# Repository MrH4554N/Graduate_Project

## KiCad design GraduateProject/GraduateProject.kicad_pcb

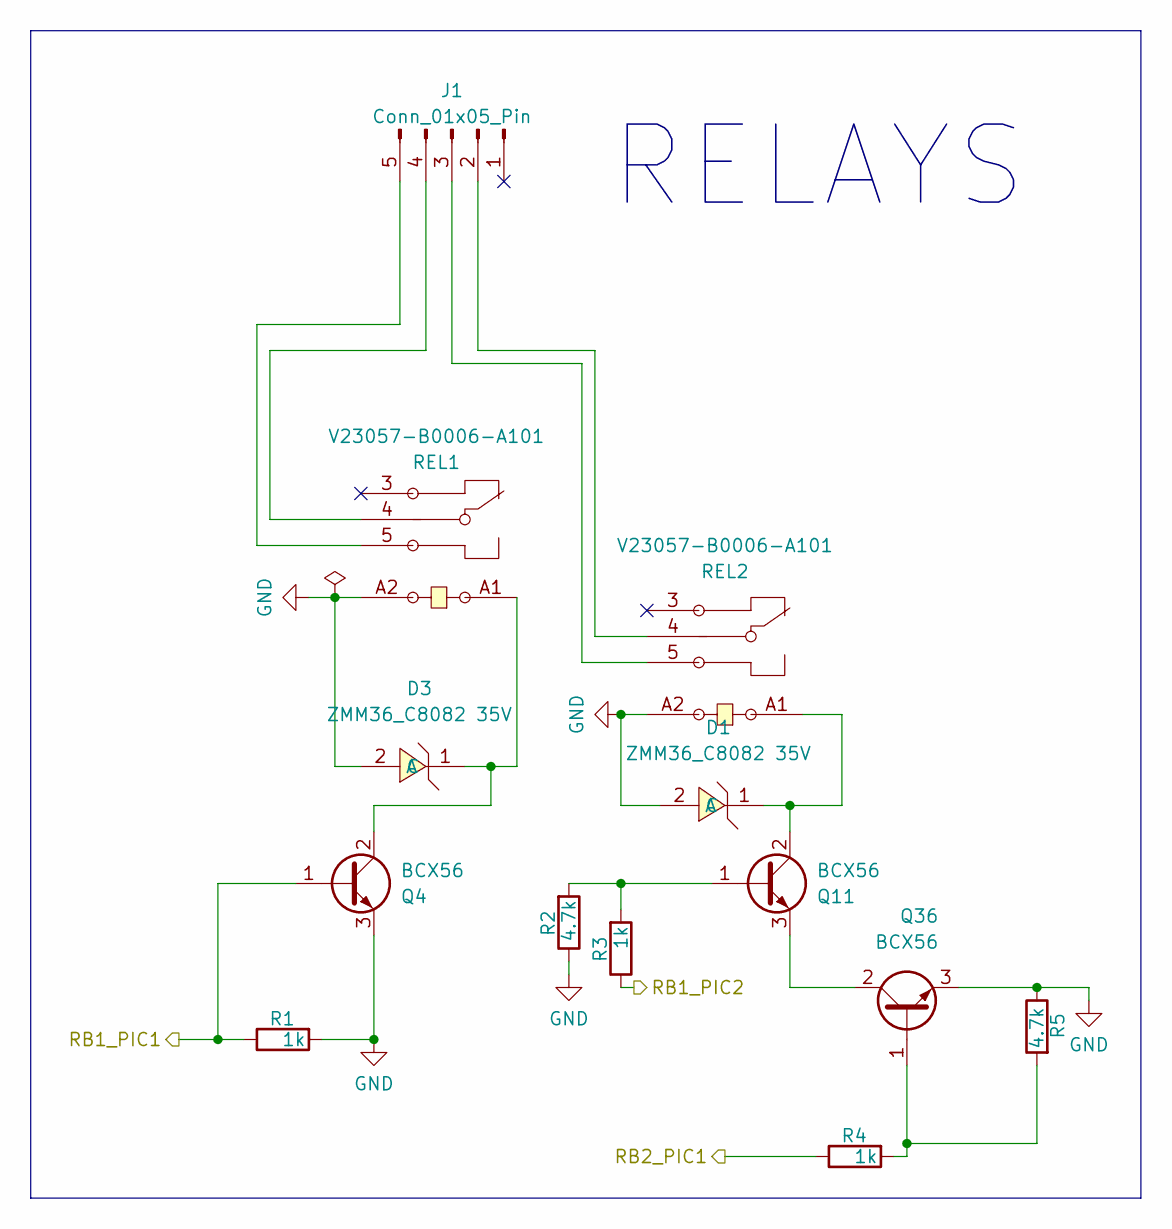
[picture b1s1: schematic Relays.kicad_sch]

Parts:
D1, D3: ZMM36_C8082 35V; LL-34_L3.5-W1.5-RD; LCSC Part C8082
J1: Conn_01x05_Pin; PinHeader_1x05_P2.54mm_Vertical
Q4, Q11, Q36: BCX56; SOT-89-3
R1, R3, R4: 1k; R_0805_2012Metric
R2, R5: 4.7k; R_0805_2012Metric
REL1, REL2: V23057-B0006-A101; RELAY-TH_TE_V23057BXXX; LCSC Part C1564084

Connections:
/PICs/RB1_PIC1: Q4.1 (B), R1.1; also elsewhere on the board
/PICs/RB1_PIC2: R3.1; also elsewhere on the board
/PICs/RB2_PIC1: R4.1; also elsewhere on the board
GND: D1.2 (A), D3.2 (A), Q4.3 (E), Q36.3 (E), R1.2, R2.1, R5.1, REL1.A2, REL2.A2; also elsewhere on the board
unnamed: D1.1 (C), Q11.2 (C), REL2.A1
unnamed: D3.1 (C), Q4.2 (C), REL1.A1
unnamed: J1.2, REL2.4
unnamed: J1.3, REL2.5
unnamed: J1.4, REL1.4
unnamed: J1.5, REL1.5
unnamed: Q11.1 (B), R2.2, R3.2
unnamed: Q11.3 (E), Q36.2 (C)
unnamed: Q36.1 (B), R4.2, R5.2

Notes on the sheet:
RELAYS

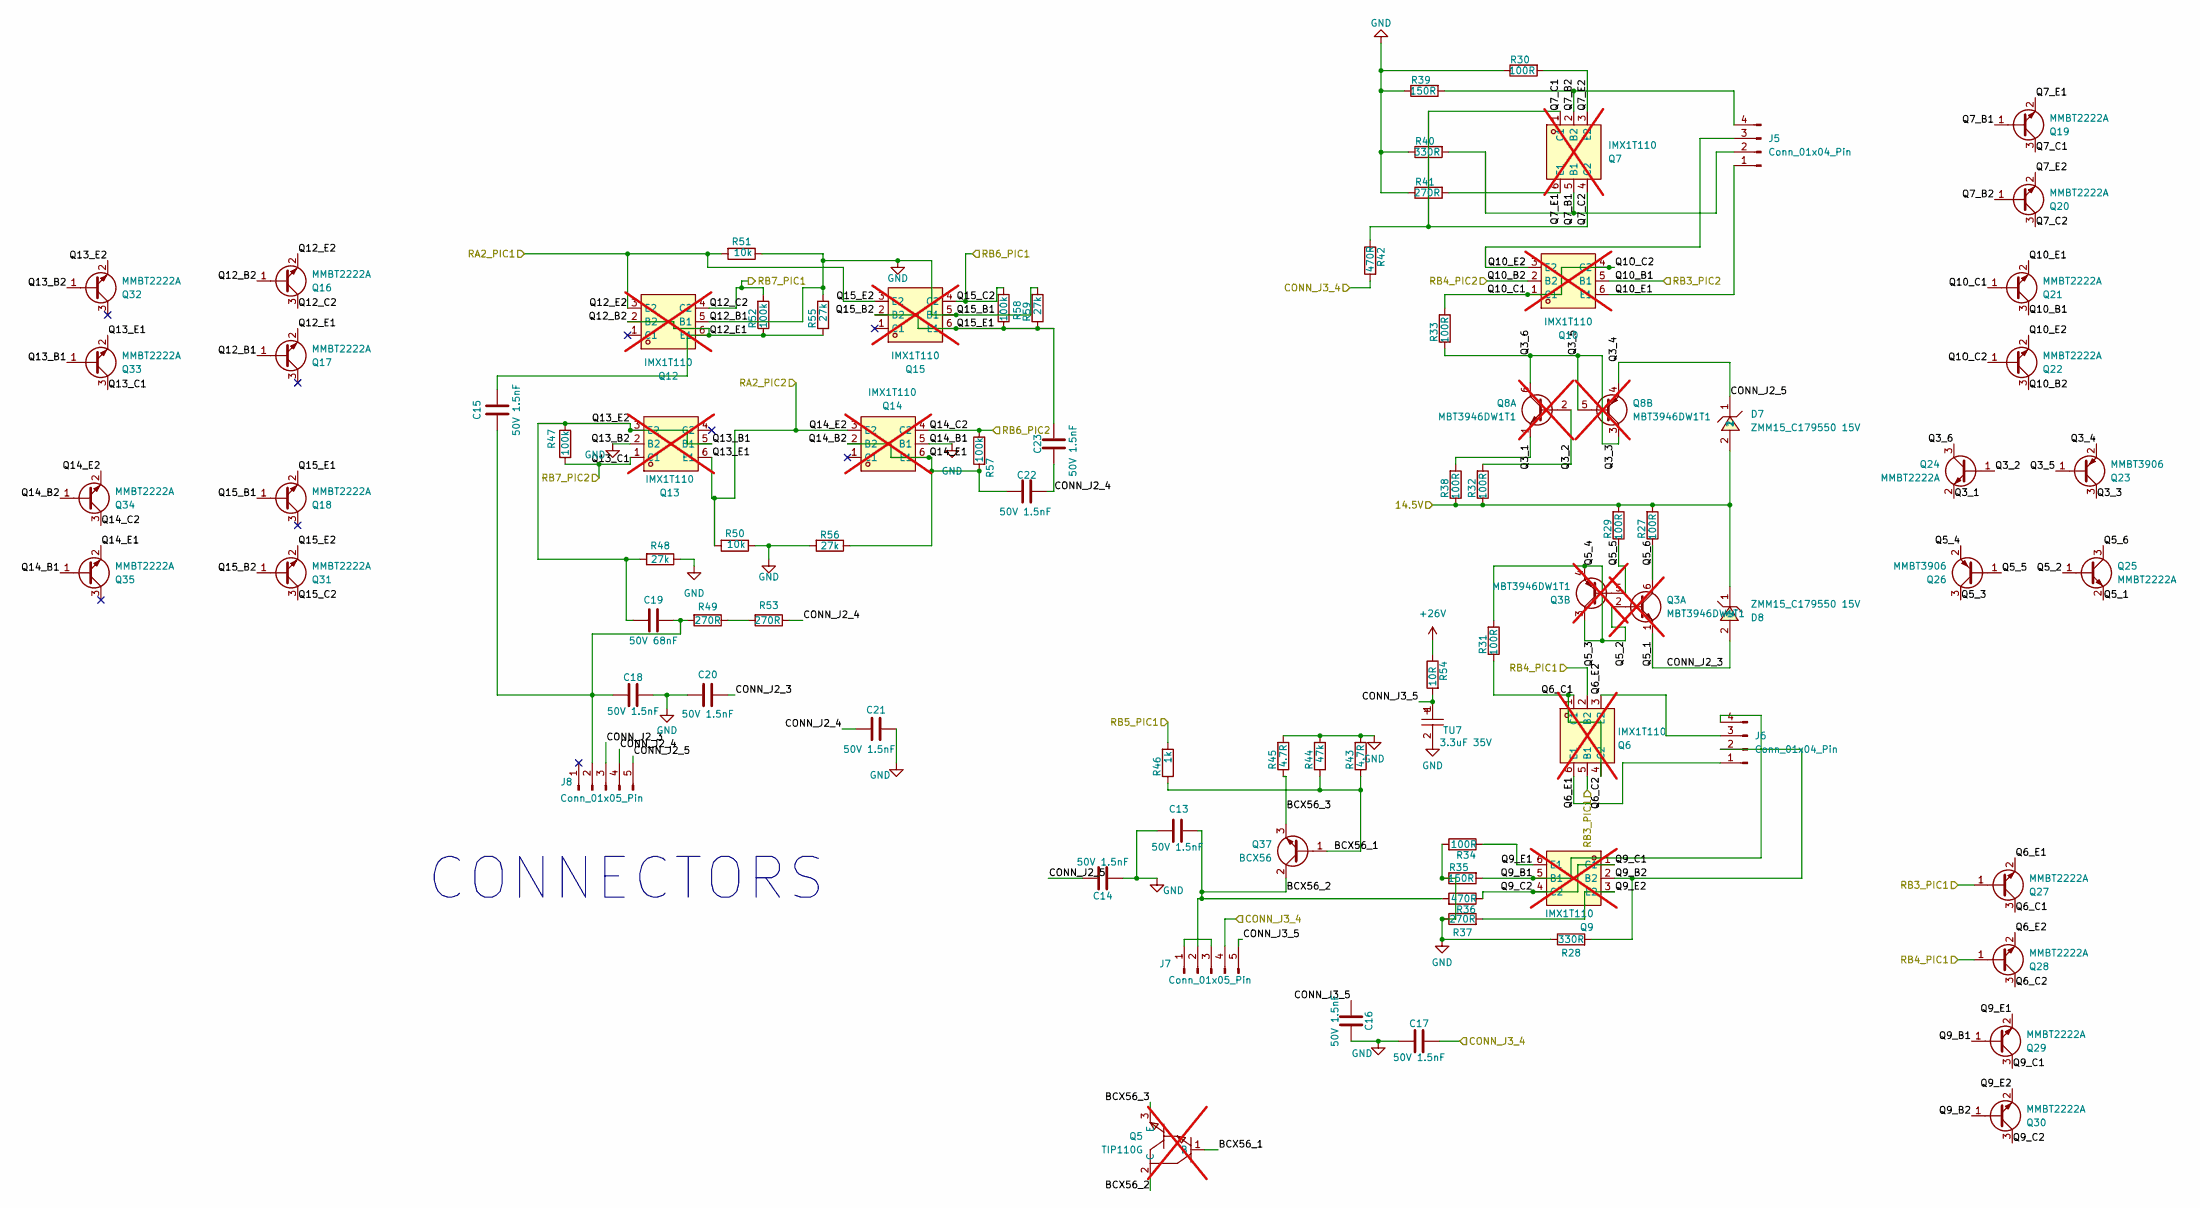
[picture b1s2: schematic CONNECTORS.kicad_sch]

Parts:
C13, C14, C15, C16, C17, C18, C20, C21, C22, C23: 50V 1.5nF; C_0805_2012Metric
C19: 50V 68nF; C_0805_2012Metric
D7, D8: ZMM15_C179550 15V; SOD-80_L3.5-W1.5-RD; LCSC Part C179550
J5, J6: Conn_01x04_Pin; PinHeader_1x04_P2.54mm_Vertical
J7, J8: Conn_01x05_Pin; PinHeader_1x05_P2.54mm_Vertical
Q3, Q8: MBT3946DW1T1; SOT-363_SC-70-6; not fitted
Q5: TIP110G; TO-220-3_L10.0-W4.5-P2.54-L; LCSC Part C233760; not fitted
Q6, Q7, Q9, Q10, Q12, Q13, Q14, Q15: IMX1T110; SOT-457_L2.9-W1.6-P0.95-LS2.80-BR; LCSC Part C509893; not fitted
Q16, Q17, Q18, Q19, Q20, Q21, Q22, Q24, Q25, Q27, Q28, Q29, Q30, Q31, Q32, Q33, Q34, Q35: MMBT2222A; SOT-23
Q23, Q26: MMBT3906; SOT-23
Q37: BCX56; SOT-89-3
R27, R29, R30, R31, R32, R33, R34, R38: 100R; R_0805_2012Metric
R28, R40: 330R; R_0805_2012Metric
R35, R39: 150R; R_0805_2012Metric
R36, R42: 470R; R_0805_2012Metric
R37, R41, R49, R53: 270R; R_0805_2012Metric
R43, R45: 4.7R; R_0805_2012Metric
R44: 47k; R_0805_2012Metric
R46: 1k; R_0805_2012Metric
R47, R52, R57, R58: 100k; R_0805_2012Metric
R48, R55, R56, R59: 27k; R_0805_2012Metric
R50, R51: 10k; R_0805_2012Metric
R54: 10R; R_0805_2012Metric
TU7: 3.3uF 35V; CAP-SMD_L3.5-W2.8-R-RD; LCSC Part C7201

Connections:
+26V: R54.1; also elsewhere on the board
/CONNECTORS/14.5V: D7.2, D8.1, R27.2, R29.2, R32.1, R38.1; also elsewhere on the board
/CONNECTORS/BCX56_1: Q5.1 (B), Q37.1 (B), R43.1, R44.1, R46.1
/CONNECTORS/BCX56_2: C13.1, J7.2, Q5.2 (C), Q37.2 (C), R36.2
/CONNECTORS/BCX56_3: Q5.3 (E), Q37.3 (E), R45.1
/CONNECTORS/CONN_J2_3: C20.1, D8.2, J8.3, Q3.1 (E1), Q25.2 (E)
/CONNECTORS/CONN_J2_4: C21.1, C22.1, C23.2, J8.4, R53.1
/CONNECTORS/CONN_J2_5: C14.1, D7.1, J8.5, Q8.4 (E2), Q23.2 (E)
/CONNECTORS/CONN_J3_4: C17.2, J7.4, R42.2; also elsewhere on the board
/CONNECTORS/CONN_J3_5: C16.1, J7.5, R54.2, TU7.1
/CONNECTORS/Q3_1: Q8.1 (E1), Q24.2 (E), R38.2
/CONNECTORS/Q3_2: Q8.2 (B1), Q24.1 (B), R32.2
/CONNECTORS/Q3_3: Q8.3 (C2), Q8.5 (B2), Q8.6 (C1), Q23.1 (B), Q23.3 (C), Q24.3 (C), R33.1
/CONNECTORS/Q5_2: Q3.2 (B1), Q3.3 (C2), Q3.4 (E2), Q25.1 (B), Q26.2 (E), Q26.3 (C), R31.2
/CONNECTORS/Q5_5: Q3.5 (B2), Q26.1 (B), R29.1
/CONNECTORS/Q5_6: Q3.6 (C1), Q25.3 (C), R27.1
/CONNECTORS/Q6_C1: Q6.1 (C1), Q6.4 (C2), Q27.3 (C), Q28.3 (C), R31.1
/CONNECTORS/Q6_E1: J6.1, Q6.6 (E1), Q27.2 (E)
/CONNECTORS/Q6_E2: J6.3, Q6.3 (E2), Q28.2 (E)
/CONNECTORS/Q7_B1: J5.2, Q7.5 (B1), Q19.1 (B), R40.2
/CONNECTORS/Q7_B2: J5.4, Q7.2 (B2), Q20.1 (B), R39.2
/CONNECTORS/Q7_C1: Q7.1 (C1), Q7.4 (C2), Q19.3 (C), Q20.3 (C), R42.1
/CONNECTORS/Q7_E1: Q7.6 (E1), Q19.2 (E), R41.2
/CONNECTORS/Q7_E2: Q7.3 (E2), Q20.2 (E), R30.2
/CONNECTORS/Q9_B1: J6.4, Q9.5 (B1), Q29.1 (B), R35.2
/CONNECTORS/Q9_B2: J6.2, Q9.2 (B2), Q30.1 (B), R28.2
/CONNECTORS/Q9_C1: Q9.1 (C1), Q9.4 (C2), Q29.3 (C), Q30.3 (C), R36.1
/CONNECTORS/Q9_E1: Q9.6 (E1), Q29.2 (E), R34.1
/CONNECTORS/Q9_E2: Q9.3 (E2), Q30.2 (E), R37.2
/CONNECTORS/Q10_B1: Q10.5 (B1), Q21.3 (C); also elsewhere on the board
/CONNECTORS/Q10_B2: Q10.2 (B2), Q22.3 (C); also elsewhere on the board
/CONNECTORS/Q10_C1: Q10.1 (C1), Q10.4 (C2), Q21.1 (B), Q22.1 (B), R33.2
/CONNECTORS/Q10_E1: J5.1, Q10.6 (E1), Q21.2 (E)
/CONNECTORS/Q10_E2: J5.3, Q10.3 (E2), Q22.2 (E)
/CONNECTORS/Q12_B2: C15.2, Q12.2 (B2), Q12.6 (E1), Q16.1 (B), Q17.2 (E), R52.1, R55.1
/CONNECTORS/Q12_C2: Q12.4 (C2), Q16.3 (C), R52.2; also elsewhere on the board
/CONNECTORS/Q12_E2: Q12.3 (E2), Q15.3 (E2), Q16.2 (E), Q31.2 (E), R51.2; also elsewhere on the board
/CONNECTORS/Q13_B1: C19.2, Q13.3 (E2), Q13.5 (B1), Q32.2 (E), Q33.1 (B), R47.1, R48.2
/CONNECTORS/Q13_C1: Q13.1 (C1), Q33.3 (C), R47.2; also elsewhere on the board
/CONNECTORS/Q13_E1: Q13.6 (E1), Q14.3 (E2), Q33.2 (E), Q34.2 (E), R50.2; also elsewhere on the board
/CONNECTORS/Q14_B2: C22.2, Q14.2 (B2), Q14.6 (E1), Q34.1 (B), Q35.2 (E), R56.1, R57.2
/CONNECTORS/Q14_C2: Q14.4 (C2), Q34.3 (C), R57.1; also elsewhere on the board
/CONNECTORS/Q15_B2: C23.1, Q15.2 (B2), Q15.6 (E1), Q18.2 (E), Q31.1 (B), R58.1, R59.1
/CONNECTORS/Q15_C2: Q15.4 (C2), Q31.3 (C), R58.2; also elsewhere on the board
/CONNECTORS/RB3_PIC1: Q6.5 (B1), Q27.1 (B); also elsewhere on the board
/CONNECTORS/RB4_PIC1: Q6.2 (B2), Q28.1 (B); also elsewhere on the board
/CONNECTORS/RB5_PIC1: R46.2; also elsewhere on the board
GND: C13.2, C14.2, C16.2, C17.1, C18.1, C20.2, C21.2, Q12.5 (B1), Q13.2 (B2), Q14.5 (B1), Q15.5 (B1), Q17.1 (B), Q18.1 (B), Q32.1 (B), Q35.1 (B), R28.1, R30.1, R34.2, R35.1, R37.1, R39.1, R40.1, R41.1, R43.2, R44.2, R45.2, R48.1, R50.1, R51.1, R55.2, R56.2, R59.2, TU7.2; also elsewhere on the board
unnamed: J7.1, J7.3
unnamed: C15.1, C18.2, C19.1, J8.2, R49.2
unnamed: R49.1, R53.2

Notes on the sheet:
CONNECTORS

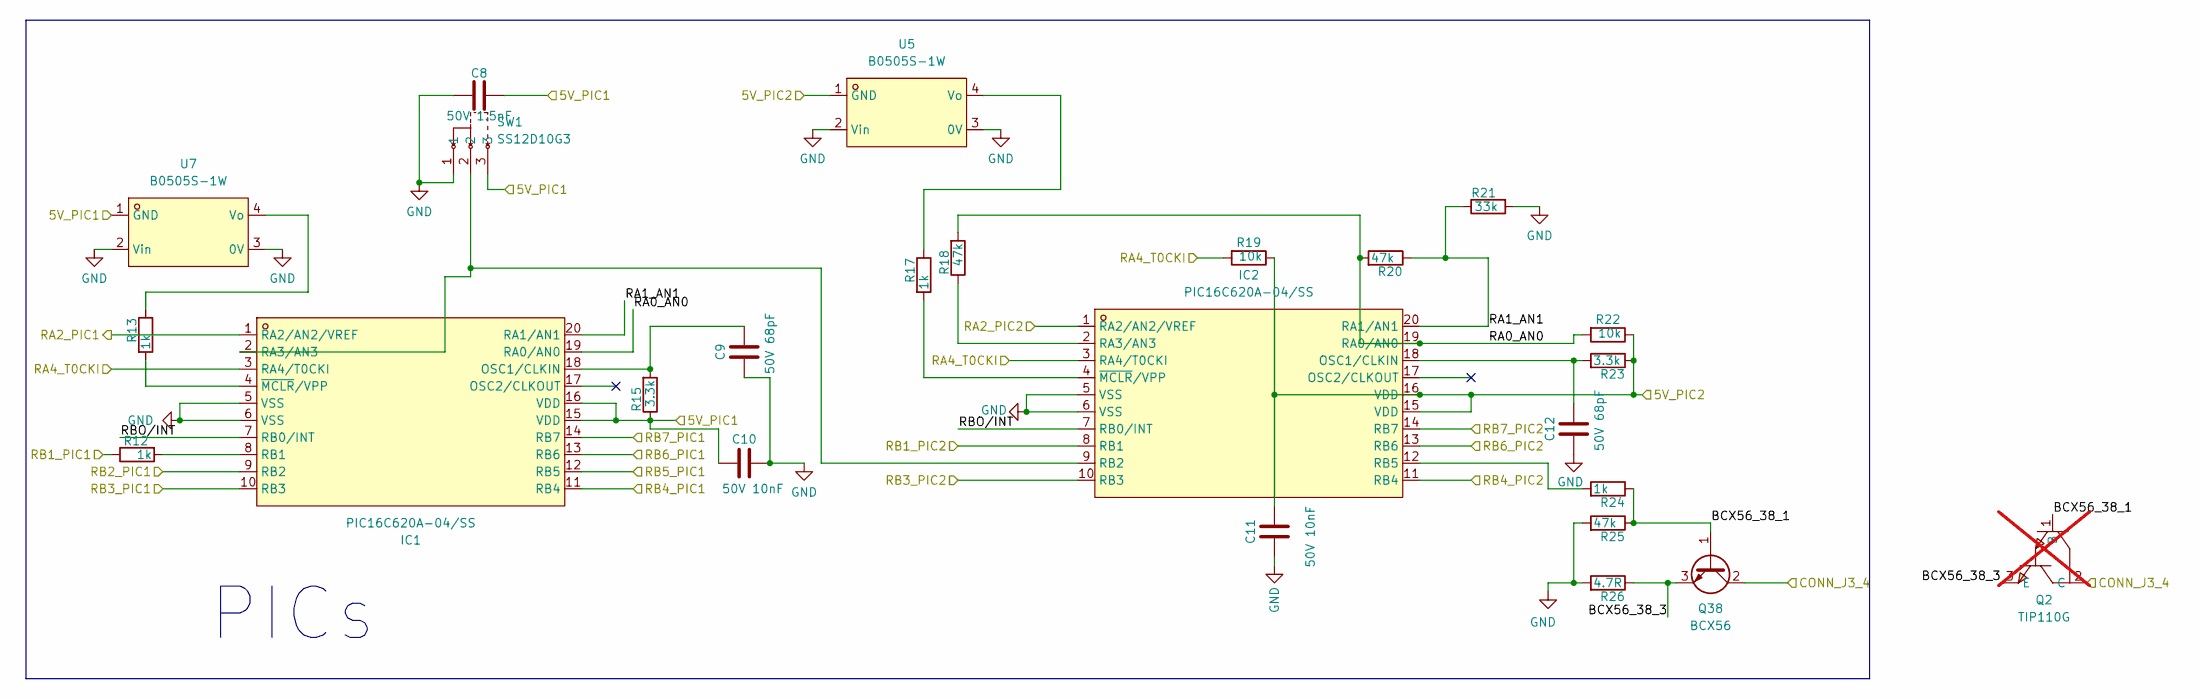
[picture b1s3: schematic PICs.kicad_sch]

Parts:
C8: 50V 1.5nF; C_0805_2012Metric
C9, C12: 50V 68pF; C_0805_2012Metric
C10, C11: 50V 10nF; C_0805_2012Metric
IC1, IC2: PIC16C620A-04/SS; SSOP-20_L7.2-W5.3-P0.65-LS7.8-BL; LCSC Part C639116
Q2: TIP110G; TO-220-3_L10.0-W4.5-P2.54-L; LCSC Part C233760; not fitted
Q38: BCX56; SOT-89-3
R12, R13, R17, R24: 1k; R_0805_2012Metric
R15, R23: 3.3k; R_0805_2012Metric
R18, R20, R25: 47k; R_0805_2012Metric
R19, R22: 10k; R_0805_2012Metric
R21: 33k; R_0805_2012Metric
R26: 4.7R; R_0805_2012Metric
SW1: SS12D10G3; SW-TH_3P-P4.8-L12.7-W6.7_SS12D10G3; LCSC Part C7431053
U5, U7: B0505S-1W; PWRM-TH_BXXXXS-1W; LCSC Part C234073

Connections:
/CONNECTORS/CONN_J3_4: Q2.2 (C), Q38.2 (C); also elsewhere on the board
/CONNECTORS/Q10_B1: IC2.10 (RB3); also elsewhere on the board
/CONNECTORS/Q10_B2: IC2.11 (RB4); also elsewhere on the board
/CONNECTORS/Q12_C2: IC1.14 (RB7); also elsewhere on the board
/CONNECTORS/Q12_E2: IC1.1 (RA2/AN2/VREF); also elsewhere on the board
/CONNECTORS/Q13_C1: IC2.14 (RB7); also elsewhere on the board
/CONNECTORS/Q13_E1: IC2.1 (RA2/AN2/VREF); also elsewhere on the board
/CONNECTORS/Q14_C2: IC2.13 (RB6); also elsewhere on the board
/CONNECTORS/Q15_C2: IC1.13 (RB6); also elsewhere on the board
/CONNECTORS/RB3_PIC1: IC1.10 (RB3); also elsewhere on the board
/CONNECTORS/RB4_PIC1: IC1.11 (RB4); also elsewhere on the board
/CONNECTORS/RB5_PIC1: IC1.12 (RB5); also elsewhere on the board
/PICs/5V_PIC1: C8.1, C10.2, IC1.15 (VDD), IC1.16 (VDD), R15.1, SW1.3, U7.1 (GND); also elsewhere on the board
/PICs/5V_PIC2: C11.1, IC2.15 (VDD), IC2.16 (VDD), R19.1, R22.1, R23.1, U5.1 (GND); also elsewhere on the board
/PICs/BCX56_38_1: Q2.1 (B), Q38.1 (B), R24.1, R25.1
/PICs/BCX56_38_3: Q2.3 (E), Q38.3 (E), R26.1
/PICs/RA0_AN0: IC1.19 (RA0/AN0), IC2.19 (RA0/AN0), R18.2, R20.2, R22.2
/PICs/RA1_AN1: IC1.20 (RA1/AN1), IC2.20 (RA1/AN1), R20.1, R21.1
/PICs/RA4_T0CKI: IC1.3 (RA4/T0CKI), IC2.3 (RA4/T0CKI), R19.2; also elsewhere on the board
/PICs/RB1_PIC1: R12.1; also elsewhere on the board
/PICs/RB1_PIC2: IC2.8 (RB1); also elsewhere on the board
/PICs/RB2_PIC1: IC1.9 (RB2); also elsewhere on the board
/PICs/RBO/INT: IC1.7 (RB0/INT), IC2.7 (RB0/INT)
GND: C8.2, C9.2, C10.1, C11.2, C12.2, IC1.5 (VSS), IC1.6 (VSS), IC2.5 (VSS), IC2.6 (VSS), R21.2, R25.2, R26.2, SW1.1, U5.2 (Vin), U5.3 (0V), U7.2 (Vin), U7.3 (0V); also elsewhere on the board
unnamed: C9.1, IC1.18 (OSC1/CLKIN), R15.2
unnamed: IC1.2 (RA3/AN3), IC2.9 (RB2), SW1.2
unnamed: IC1.8 (RB1), R12.2
unnamed: IC1.4 (~MCLR/VPP), R13.2
unnamed: C12.1, IC2.18 (OSC1/CLKIN), R23.2
unnamed: IC2.2 (RA3/AN3), R18.1
unnamed: IC2.12 (RB5), R24.2
unnamed: IC2.4 (~MCLR/VPP), R17.2
unnamed: R17.1, U5.4 (Vo)
unnamed: R13.1, U7.4 (Vo)

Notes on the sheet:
PICs

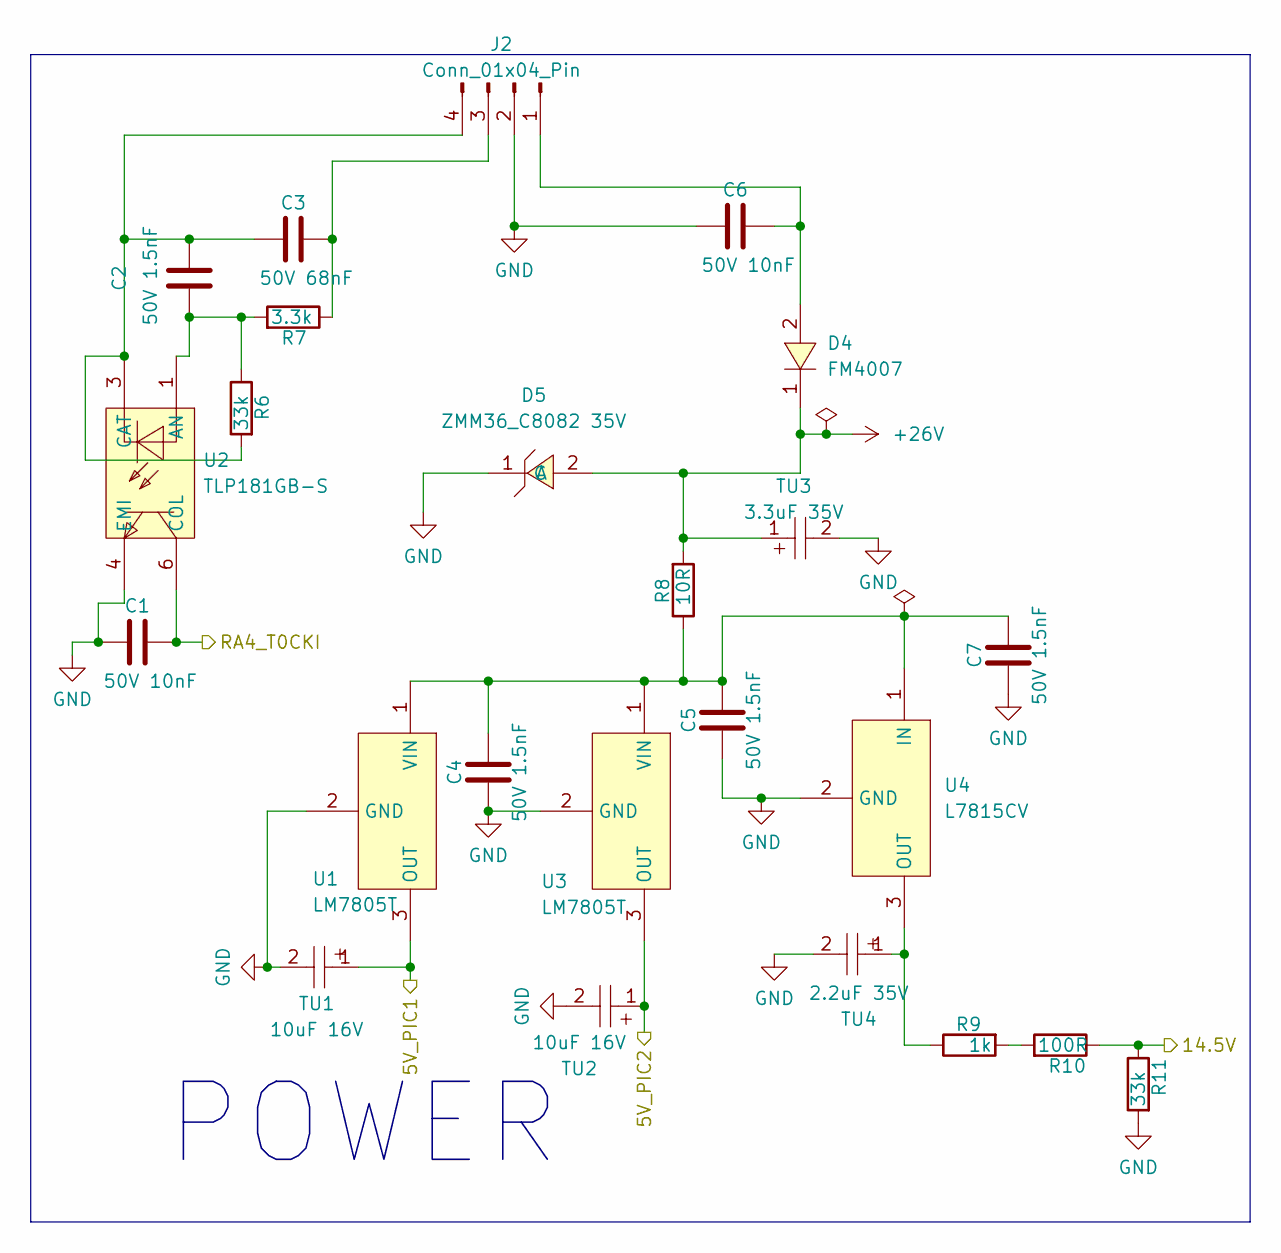
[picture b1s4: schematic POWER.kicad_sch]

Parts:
C1: 50V 10nF; C_0805_2012Metric
C2, C4, C5, C7: 50V 1.5nF; C_0805_2012Metric
C3: 50V 68nF; C_0805_2012Metric
C6: 50V 10nF; C_1206_3216Metric
D4: FM4007; SOD-123FL_L2.7-W1.8-LS3.8-RD; LCSC Part C402244
D5: ZMM36_C8082 35V; LL-34_L3.5-W1.5-RD; LCSC Part C8082
J2: Conn_01x04_Pin; PinHeader_1x04_P2.54mm_Vertical
R6, R11: 33k; R_0805_2012Metric
R7: 3.3k; R_0805_2012Metric
R8: 10R; R_0805_2012Metric
R9: 1k; R_0805_2012Metric
R10: 100R; R_0805_2012Metric
TU1, TU2: 10uF 16V; CAP-SMD_L3.2-W1.6-RD-C7171; LCSC Part C7171
TU3: 3.3uF 35V; CAP-SMD_L3.5-W2.8-R-RD; LCSC Part C7201
TU4: 2.2uF 35V; CAP-SMD_L3.5-W2.8-R-RD; LCSC Part C19276
U1, U3: LM7805T; TO-220-3_L10.0-W4.5-P2.54-L; LCSC Part C507145
U2: TLP181GB-S; SOP-4_L3.7-W4.6-P2.54-LS7.0-TL; LCSC Part C388374
U4: L7815CV; TO-220-3_L10.0-W4.5-P2.54-L; LCSC Part C5676

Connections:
+26V: D4.1 (C), D5.2 (A), R8.2, TU3.1; also elsewhere on the board
/CONNECTORS/14.5V: R10.1, R11.1; also elsewhere on the board
/PICs/5V_PIC1: TU1.1, U1.3 (OUT); also elsewhere on the board
/PICs/5V_PIC2: TU2.1, U3.3 (OUT); also elsewhere on the board
/PICs/RA4_T0CKI: C1.1, U2.6 (COL); also elsewhere on the board
GND: C1.2, C4.2, C5.2, C6.2, C7.2, D5.1 (C), J2.2, R11.2, TU1.2, TU2.2, TU3.2, TU4.2, U1.2 (GND), U2.4 (EMI), U3.2 (GND), U4.2 (GND); also elsewhere on the board
unnamed: C6.1, D4.2 (A), J2.1
unnamed: C3.1, J2.3, R7.1
unnamed: C2.1, C3.2, J2.4, R6.2, U2.3 (CAT)
unnamed: R9.2, R10.2
unnamed: C4.1, C5.1, C7.1, R8.1, U1.1 (VIN), U3.1 (VIN), U4.1 (IN)
unnamed: C2.2, R6.1, R7.2, U2.1 (AN)
unnamed: R9.1, TU4.1, U4.3 (OUT)

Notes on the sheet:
POWER

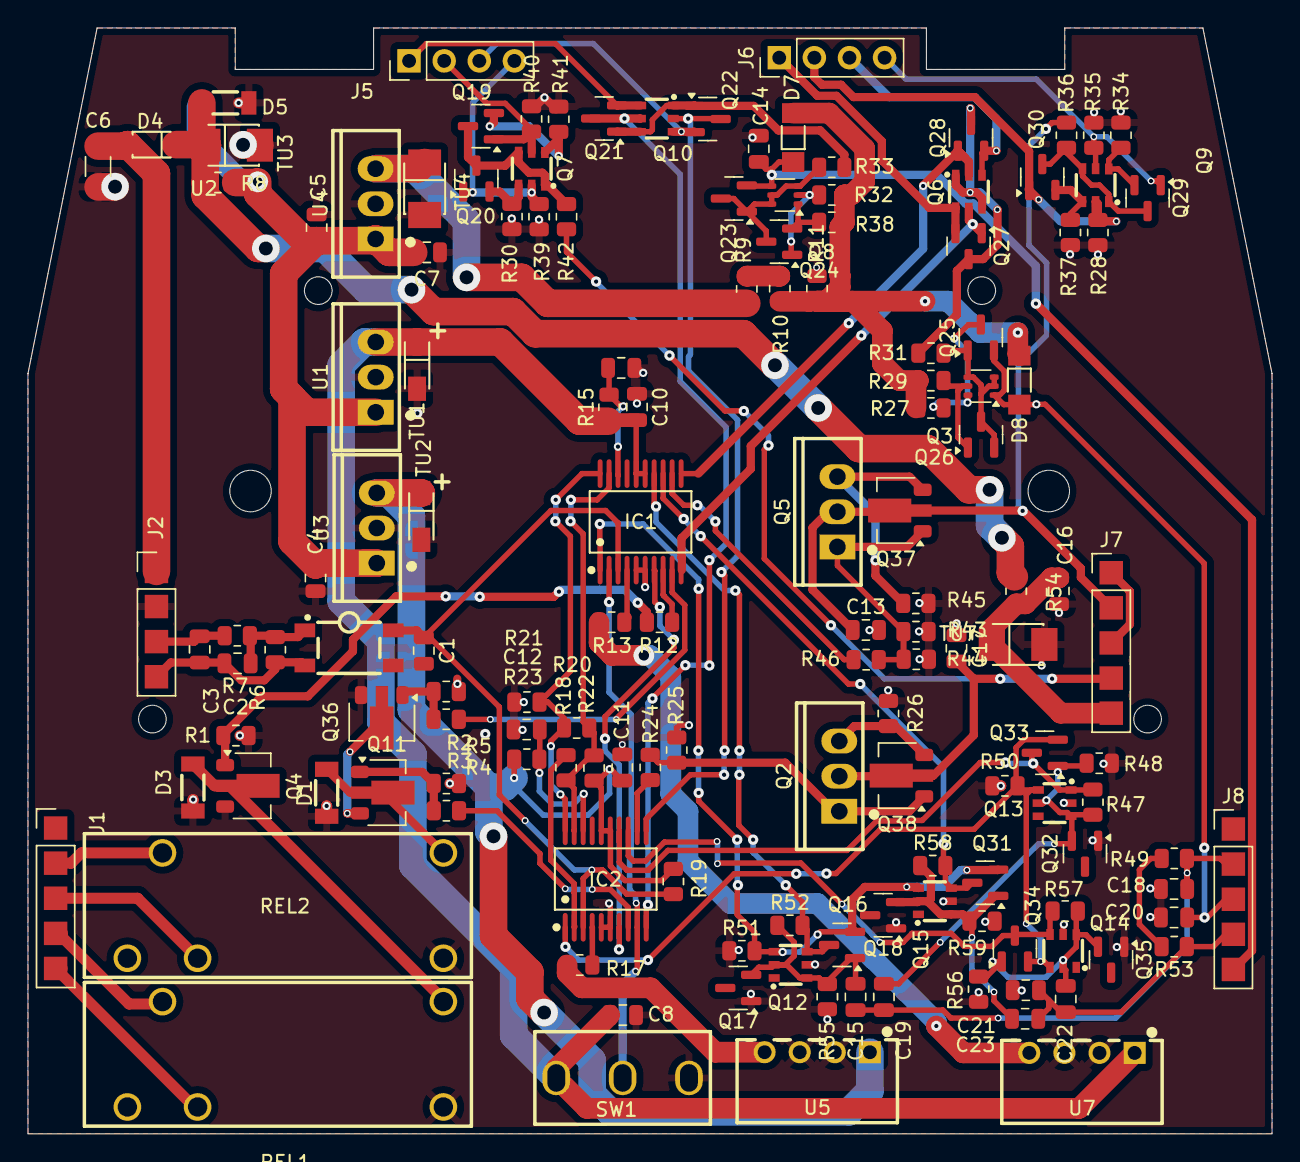
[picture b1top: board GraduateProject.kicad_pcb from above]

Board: 2 copper layers, 90.0 x 80.0 mm, 145 parts (0 on the bottom side), 88 nets.

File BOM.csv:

Reference,Qty,Value,DNP,Exclude from BOM,Exclude from Board,Footprint,Description,Main Version,Split Transistor Version,Buying link
"C1,C10,C11",3,50V 10nF,,,,Capacitor_SMD:C_0805_2012Metric,Capacitor 50V 10nF 0805,,,https://www.thegioiic.com/tu-gom-0805-10nf-50v
"C2,C4,C5,C7,C8,C13,C14,C15,C16,C17,C18,C20,C21,C22,C23",15,50V 1.5nF,,,,Capacitor_SMD:C_0805_2012Metric,Capacitor 50V 1.5nF 0805,,,https://www.thegioiic.com/tu-gom-0805-1-5nf-50v
"C3,C19",2,50V 68nF,,,,Capacitor_SMD:C_0805_2012Metric,Capacitor 50V 68nF 0805,,,https://www.thegioiic.com/tu-gom-0805-68nf-50v
C6,1,50V 10nF,,,,Capacitor_SMD:C_1206_3216Metric,Capacitor 50V 10nF 1206,,,https://www.thegioiic.com/tu-gom-1206-10nf-50v
"C9,C12",2,50V 68pF,,,,Capacitor_SMD:C_0805_2012Metric,Capacitor 50V 68pF 0805,,,https://www.thegioiic.com/tu-gom-0805-68pf-50v
"D1,D3,D5",3,ZMM36_C8082 35V,,,,easyeda2kicad:LL-34_L3.5-W1.5-RD,Diode ZMM36 35V,,,https://www.thegioiic.com/zmm36-diode-zener-36v-500mw-sod-80
D4,1,FM4007,,,,easyeda2kicad:SOD-123FL_L2.7-W1.8-LS3.8-RD,Diode FM4007,,,https://www.thegioiic.com/twgmc-1n4007-m7-sma-diode-chinh-lu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
"D7,D8",2,ZMM15_C179550 15V,,,,easyeda2kicad:SOD-80_L3.5-W1.5-RD,Diode ZMM15 15V,,,https://www.thegioiic.com/zmm15-diode-zener-15v-500mw-smd
"IC1,IC2",2,PIC16C620A-04/SS,,,,easyeda2kicad:SSOP-20_L7.2-W5.3-P0.65-LS7.8-BL,PIC16C620A-04/SS,,,https://jlcpcb.com/partdetail/MicrochipTech-PIC16C620A_04SS/C639116
"J1,J7,J8",3,Conn_01x05_Pin,,,,Connector_PinHeader_2.54mm:PinHeader_1x05_P2.54mm_Vertical,"Generic connector, single row, 01x05, script generated",,,
"J2,J5,J6",3,Conn_01x04_Pin,,,,Connector_PinHeader_2.54mm:PinHeader_1x04_P2.54mm_Vertical,"Generic connector, single row, 01x04, script generated",,,
"Q2,Q5",2,TIP110G,DNP,,,easyeda2kicad:TO-220-3_L10.0-W4.5-P2.54-L,NPN Darlington transistor TIP110G,,,https://www.thegioiic.com/tip110-transistor-npn-1-ngo-ra-dar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
"Q3,Q8",2,MBT3946DW1T1,DNP,,,Package_TO_SOT_SMD:SOT-363_SC-70-6,"200mA IC, 40V Vce, Dual NPN/PNP Transistors, SOT-363 MBT3946DW1T1",Main,,https://jlcpcb.com/partdetail/LRC-LMBT3946DW1T1G/C136169
"Q4,Q11,Q36,Q37,Q38",5,BCX56,,,,Package_TO_SOT_SMD:SOT-89-3,"1A Ic, 80V Vce, NPN Medium Power Transistor, SOT-89 BCX56",,,https://jlcpcb.com/partdetail/25020-BCX56_RANGE_100_250/C24280
"Q6,Q7,Q9,Q10,Q12,Q13,Q14,Q15",8,IMX1T110,DNP,,,easyeda2kicad:SOT-457_L2.9-W1.6-P0.95-LS2.80-BR,NPN transistor IMX1T110,Main,,https://jlcpcb.com/partdetail/ROHMSemicon-IMX1T110/C509893
"Q16,Q17,Q18,Q19,Q20,Q21,Q22,Q24,Q25,Q27,Q28,Q29,Q30,Q31,Q32,Q33,Q34,Q35",18,MMBT2222A,,,,Package_TO_SOT_SMD:SOT-23,"600mA Ic, 40V Vce, NPN Transistor, SOT-23",,Split,https://www.thegioiic.com/mmbt2222a-1p-transistor-npn-40v-0-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
"Q23,Q26",2,MMBT3906,,,,Package_TO_SOT_SMD:SOT-23,"-0.2A Ic, -40V Vce, Small Signal PNP Transistor, SOT-23",,Split,https://www.thegioiic.com/mmbt3906-transistor-pnp-40v-0-2a-3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
"R1,R3,R4,R9,R12,R13,R17,R24,R46",9,1k,,,,Resistor_SMD:R_0805_2012Metric,Resistor 1k 0805,,,https://www.thegioiic.com/dien-tro-1-kohm-0805-1-
"R2,R5",2,4.7k,,,,Resistor_SMD:R_0805_2012Metric,Resistor 4.7k 0805,,,https://www.thegioiic.com/dien-tro-4-7-kohm-0805-1-
"R6,R11,R21",3,33k,,,,Resistor_SMD:R_0805_2012Metric,Resistor 33k 0805,,,https://www.thegioiic.com/dien-tro-33-kohm-0805-1-
"R7,R15,R23",3,3.3k,,,,Resistor_SMD:R_0805_2012Metric,Resistor 3.3k 0805,,,https://www.thegioiic.com/dien-tro-3-3-kohm-0805-1-
"R8,R54",2,10R,,,,Resistor_SMD:R_0805_2012Metric,Resistor 10R 0805,,,https://www.thegioiic.com/dien-tro-10-ohm-0805-1-
"R10,R27,R29,R30,R31,R32,R33,R34,R38",9,100R,,,,Resistor_SMD:R_0805_2012Metric,Resistor 100R 0805,,,https://www.thegioiic.com/dien-tro-100-ohm-0805-1-
"R18,R20,R25,R44",4,47k,,,,Resistor_SMD:R_0805_2012Metric,Resistor 47k 0805,,,https://www.thegioiic.com/dien-tro-47-kohm-0805-1-
"R19,R22,R50,R51",4,10k,,,,Resistor_SMD:R_0805_2012Metric,Resistor 10k 0805,,,https://www.thegioiic.com/dien-tro-10-kohm-0805-1-
"R26,R43,R45",3,4.7R,,,,Resistor_SMD:R_0805_2012Metric,Resistor 4.7R 0805,,,https://www.thegioiic.com/dien-tro-4-7-ohm-0805-5-
"R28,R40",2,330R,,,,Resistor_SMD:R_0805_2012Metric,Resistor 330R 0805,,,https://www.thegioiic.com/dien-tro-330-ohm-0805-1-
"R35,R39",2,150R,,,,Resistor_SMD:R_0805_2012Metric,Resistor 150R 0805,,,https://www.thegioiic.com/dien-tro-150-ohm-0805-5-
"R36,R42",2,470R,,,,Resistor_SMD:R_0805_2012Metric,Resistor 470R 0805,,,https://www.thegioiic.com/dien-tro-470-ohm-0805-1-
"R37,R41,R49,R53",4,270R,,,,Resistor_SMD:R_0805_2012Metric,Resistor 270R 0805,,,https://www.thegioiic.com/dien-tro-270-ohm-0805-5-
"R47,R52,R57,R58",4,100k,,,,Resistor_SMD:R_0805_2012Metric,Resistor 100k 0805,,,https://www.thegioiic.com/dien-tro-100-kohm-0805-1-
"R48,R55,R56,R59",4,27k,,,,Resistor_SMD:R_0805_2012Metric,Resistor 27k 0805,,,https://www.thegioiic.com/dien-tro-27-kohm-0805-5-
"REL1,REL2",2,V23057-B0006-A101,,,,easyeda2kicad:RELAY-TH_TE_V23057BXXX,Relay V23057-B0006-A101,,,https://jlcpcb.com/partdetail/TEConnectivity-V23057_B0006A10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
SW1,1,SS12D10G3,,,,easyeda2kicad:SW-TH_3P-P4.8-L12.7-W6.7_SS12D10G3,Switch SS12D10G3,,,https://www.thegioiic.com/ss12d00g4-cong-tac-truot-3-chan-xu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
"TU1,TU2",2,10uF 16V,,,,easyeda2kicad:CAP-SMD_L3.2-W1.6-RD-C7171,Capacitor tantalum 10uF 16V,,,https://www.thegioiic.com/tu-tantalum-10uf-16v-2312-tajc106k016rnj
"TU3,TU7",2,3.3uF 35V,,,,easyeda2kicad:CAP-SMD_L3.5-W2.8-R-RD,Capacitor tantalum 3.3uF 35V,,,https://jlcpcb.com/partdetail/-TAJC335K035RNJ/C22230
TU4,1,2.2uF 35V,,,,easyeda2kicad:CAP-SMD_L3.5-W2.8-R-RD,Capacitor tantalum 2.2uF 35V,,,https://jlcpcb.com/partdetail/-TAJB225K035RNJ/C19276
"U1,U3",2,LM7805T,,,,easyeda2kicad:TO-220-3_L10.0-W4.5-P2.54-L,Regulator 5V LM7805T,,,https://www.thegioiic.com/lm7805t-ic-on-ap-5v-1-5a-to-220-3
U2,1,TLP181GB-S,,,,easyeda2kicad:SOP-4_L3.7-W4.6-P2.54-LS7.0-TL,Optoisolator TLP181GB-S,,,https://jlcpcb.com/partdetail/363305-TLP181GB_S_UMW/C388374
U4,1,L7815CV,,,,easyeda2kicad:TO-220-3_L10.0-W4.5-P2.54-L,Regulator 15V L7815CV,,,https://www.thegioiic.com/l7815cv-ic-on-ap-15v-1-5a
"U5,U7",2,B0505S-1W,,,,easyeda2kicad:PWRM-TH_BXXXXS-1W,Regulator 5V B0505S-1W,,,https://www.thegioiic.com/b0505s-1wr3-chuyen-doi-dc-dc-vao-5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
,,,,,,,,,,
,,,,,,,,Chú thích,,Chú thích
,,,,,,,,Dùng cho c? 2 phiên b?n,,thegioiic.com
,,,,,,,,Phiên b?n không tách transistor ,,jlcpcb.com
,,,,,,,,Phiên b?n tách transistor,,

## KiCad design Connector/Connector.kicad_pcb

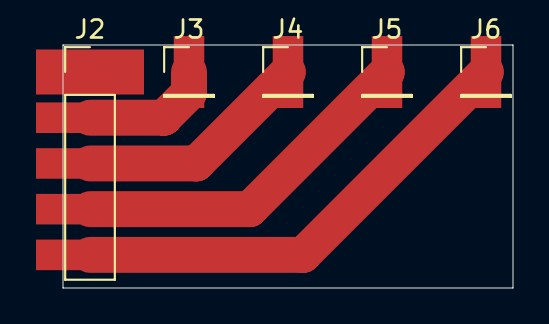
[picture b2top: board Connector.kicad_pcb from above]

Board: 2 copper layers, 25.0 x 13.5 mm, 5 parts (0 on the bottom side), 4 nets.

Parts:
J2: Conn_01x05_Pin; PinHeader_1x05_P2.54mm_Vertical
J3, J4, J5, J6: Conn_01x01_Pin; PinHeader_1x01_P2.54mm_Vertical

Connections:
unnamed: J2.2, J3.1
unnamed: J2.3, J4.1
unnamed: J2.4, J5.1
unnamed: J2.e (Pin_5), J6.1

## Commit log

2025-08-20 Add files via upload
    20/8/25-Hardware Design
2025-08-21 Add files via upload
    21/8/25
2025-09-02 2/9/25
2025-09-03 3/9/25
2025-09-10 Add files via upload
    10/9/25
2025-09-10 Add files via upload
    Add BOM
2025-09-11 Add files via upload
    11/9/25
2025-09-11 Add files via upload
    17h37 11/9/2025
2025-09-12 Add files via upload
    18h02 12/9/25
2025-09-13 Add files via upload
    13/9/25
2025-09-22 Add files via upload
    13h20 22/9/25
2025-10-05 Add files via upload
    5/10/25
